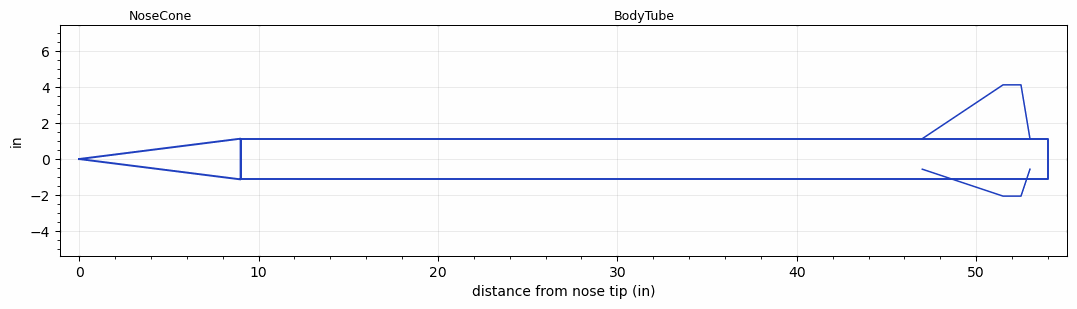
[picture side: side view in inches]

<RASAeroDocument>
 <FileVersion>2</FileVersion>
 <RocketDesign>
  <NoseCone>
   <Length>9</Length>
   <Diameter>2.27</Diameter>
   <Shape>Conical</Shape>
   <Location>0</Location>
  </NoseCone>
  <BodyTube>
   <Length>45</Length>
   <Diameter>2.27</Diameter>
   <LaunchLugDiameter>0.5</LaunchLugDiameter>
   <LaunchLugLength>0.5</LaunchLugLength>
   <Location>9</Location>
   <Fin>
    <Count>3</Count>
    <Chord>6</Chord>
    <Span>3</Span>
    <SweepDistance>4.5</SweepDistance>
    <TipChord>1</TipChord>
    <Thickness>0.07</Thickness>
    <LERadius>0.01</LERadius>
    <Location>7</Location>
    <AirfoilSection>Single Wedge</AirfoilSection>
   </Fin>
  </BodyTube>
  <Surface>Cast Iron (Very Rough)</Surface>
  <ModifiedBarrowman>False</ModifiedBarrowman>
  <Turbulence>False</Turbulence>
  <UseBooster1>False</UseBooster1>
  <UseBooster2>False</UseBooster2>
 </RocketDesign>
 <LaunchSite>
  <Altitude>0</Altitude>
  <Pressure>0</Pressure>
  <RodAngle>0</RodAngle>
  <RodLength>4</RodLength>
  <Temperature>75</Temperature>
  <WindSpeed>0</WindSpeed>
 </LaunchSite>
 <Recovery>
  <Altitude1>1000</Altitude1>
  <Altitude2>1000</Altitude2>
  <DeviceType1>None</DeviceType1>
  <DeviceType2>None</DeviceType2>
  <Event1>False</Event1>
  <Event2>False</Event2>
  <Size1>1</Size1>
  <Size2>1</Size2>
  <EventType1>None</EventType1>
  <EventType2>None</EventType2>
  <CD1>1.33</CD1>
  <CD2>1.33</CD2>
 </Recovery>
 <SimulationList>
  <Simulation>
   <SustainerEngine>H242T  (AT)</SustainerEngine>
   <SustainerLaunchWt>4.63</SustainerLaunchWt>
   <SustainerNozzleDiameter>0.5</SustainerNozzleDiameter>
   <SustainerCG>31</SustainerCG>
   <SustainerIgnitionDelay>0</SustainerIgnitionDelay>
   <Booster1SeparationDelay>0</Booster1SeparationDelay>
   <Booster1IgnitionDelay>0</Booster1IgnitionDelay>
   <IncludeBooster1>False</IncludeBooster1>
   <Booster2Delay>0</Booster2Delay>
   <IncludeBooster2>False</IncludeBooster2>
   <TimetoApogee>10.56015</TimetoApogee>
   <MaxAltitude>1707.378</MaxAltitude>
   <MaxVelocity>336.1714</MaxVelocity>
  </Simulation>
  <Simulation>
   <SustainerEngine>J1999N  (AT)</SustainerEngine>
   <SustainerLaunchWt>6.5</SustainerLaunchWt>
   <SustainerNozzleDiameter>0.5</SustainerNozzleDiameter>
   <SustainerCG>35</SustainerCG>
   <SustainerIgnitionDelay>0</SustainerIgnitionDelay>
   <Booster1SeparationDelay>0</Booster1SeparationDelay>
   <Booster1IgnitionDelay>0</Booster1IgnitionDelay>
   <IncludeBooster1>False</IncludeBooster1>
   <Booster2Delay>0</Booster2Delay>
   <IncludeBooster2>False</IncludeBooster2>
   <TimetoApogee>20.16037</TimetoApogee>
   <MaxAltitude>8924.447</MaxAltitude>
   <MaxVelocity>1438.83</MaxVelocity>
  </Simulation>
  <Simulation>
   <SustainerEngine>J1799N  (AT)</SustainerEngine>
   <SustainerLaunchWt>6.37</SustainerLaunchWt>
   <SustainerCG>31.8</SustainerCG>
   <SustainerIgnitionDelay>0</SustainerIgnitionDelay>
   <Booster1SeparationDelay>0</Booster1SeparationDelay>
   <Booster1IgnitionDelay>0</Booster1IgnitionDelay>
   <IncludeBooster1>False</IncludeBooster1>
   <Booster2Delay>0</Booster2Delay>
   <IncludeBooster2>False</IncludeBooster2>
   <TimetoApogee>19.33035</TimetoApogee>
   <MaxAltitude>8051.797</MaxAltitude>
   <MaxVelocity>1282.627</MaxVelocity>
  </Simulation>
 </SimulationList>
</RASAeroDocument>
